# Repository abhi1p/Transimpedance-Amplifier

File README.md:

# Transimpedance-Amplifier
Transimpedance Amplifier PCB using NE5532 OP-Amp IC

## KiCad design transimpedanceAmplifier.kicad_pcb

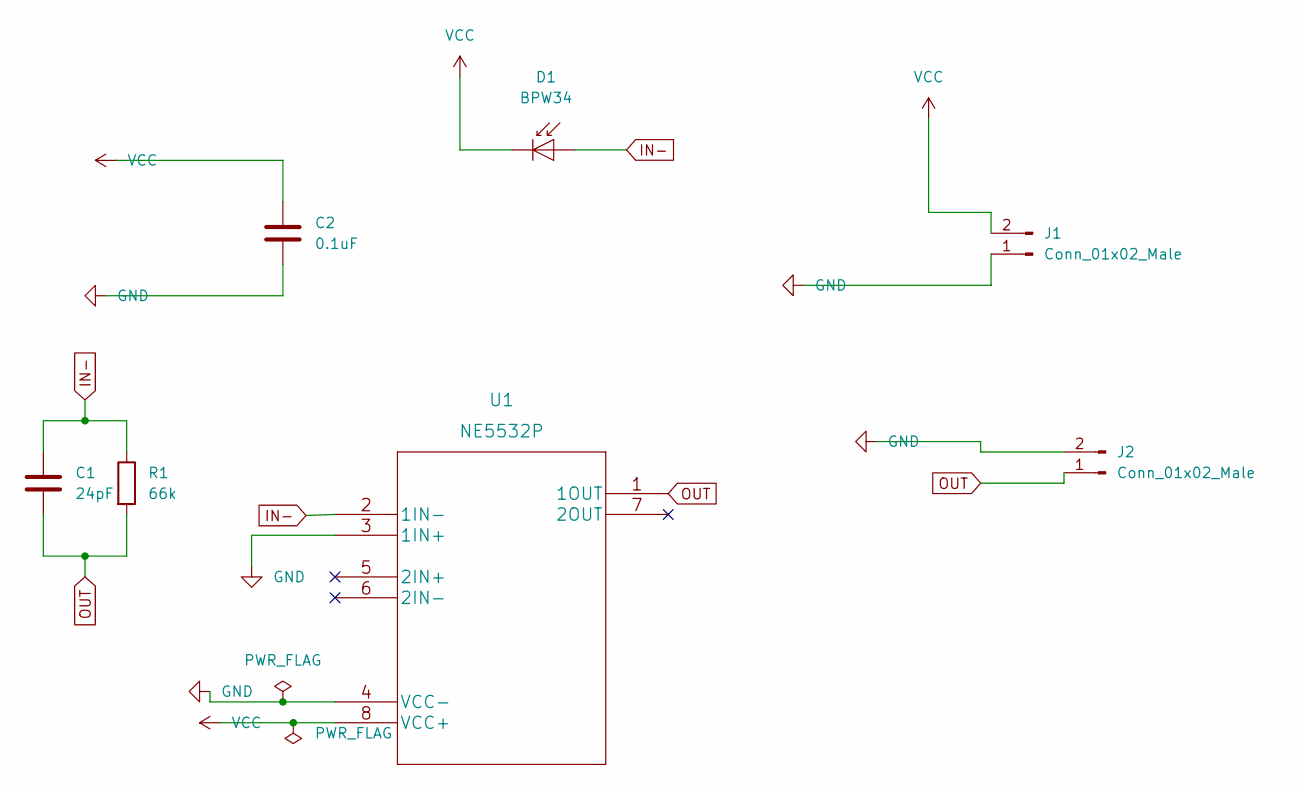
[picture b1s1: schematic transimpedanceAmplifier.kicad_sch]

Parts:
C1: 24pF; C_0201_0603Metric
C2: 0.1uF; C_0201_0603Metric
D1: BPW34; Osram_DIL2_4.3x4.65mm_P5.08mm
J1, J2: Conn_01x02_Male; AMASS_XT30U-F_1x02_P5.0mm_Vertical
R1: 66k; R_0201_0603Metric
U1: NE5532P

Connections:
GND: C2.2, J1.1, J2.2, U1.3 (1IN+), U1.4 (VCC-)
IN-: C1.1, D1.2 (A), R1.1, U1.2 (1IN-)
OUT: C1.2, J2.1, R1.2, U1.1 (1OUT)
VCC: C2.1, D1.1 (K), J1.2, U1.8 (VCC+)

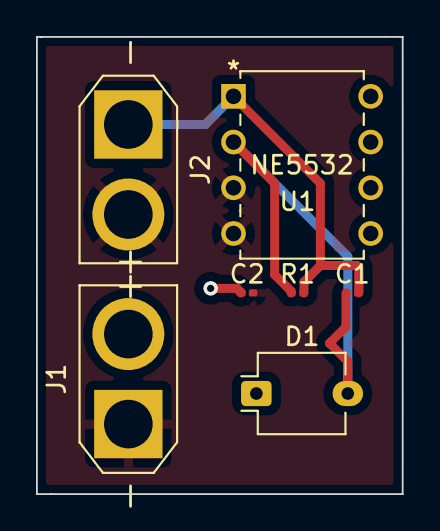
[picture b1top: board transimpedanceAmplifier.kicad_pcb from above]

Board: 2 copper layers, 20.3 x 25.4 mm, 7 parts (0 on the bottom side), 4 nets.

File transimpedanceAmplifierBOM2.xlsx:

Source: | E:\Development\PCB\LIFI\transimpedanceAmplifier\transimpedanceAmplifier.kicad_s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
Date: | 44758.579791666663
Tool: | Eeschema (6.0.6)
Generator: | E:\Software\KiCad\6.0\bin\scripting\plugins/bom_csv_grouped_by_value_with_fp.py
Component Count: | 7
Ref | Qnty | Value | Cmp name | Footprint | Description | Vendor
C1, | 1 | 24pF | C | Capacitor_SMD:C_0201_0603Metric | Unpolarized capacitor
C2, | 1 | 0.1uF | C | Capacitor_SMD:C_0201_0603Metric | Unpolarized capacitor
D1, | 1 | BPW34 | BPW34 | OptoDevice:Osram_DIL2_4.3x4.65mm_P5.08mm | Silicon PIN Photodiode
J1, J2, | 2 | Conn_01x02_Male | Conn_01x02_Male | Connector_AMASS:AMASS_XT30U-F_1x02_P5.0mm_Vertical | Generic connector, single row, 01x02, script generated (kicad-library-utils/sch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
R1, | 1 | 66k | R | Resistor_SMD:R_0201_0603Metric | Resistor
U1, | 1 | NE5532P | NE5532P | Package_DIP:NE5532P

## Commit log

2022-08-28 Create Gerber
2022-08-28 Create test

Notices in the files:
parts and their libraries:
Copyright 2021 Accelerated Designs. All rights reserved.
